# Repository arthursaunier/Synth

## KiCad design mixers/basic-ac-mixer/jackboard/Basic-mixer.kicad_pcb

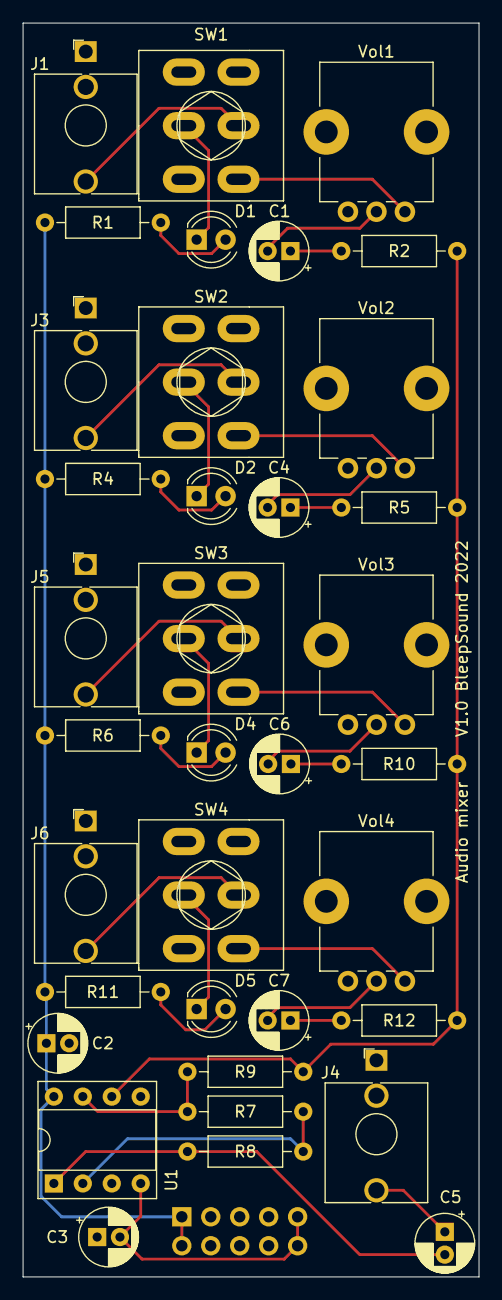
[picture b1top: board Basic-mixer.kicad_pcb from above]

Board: 2 copper layers, 40.0 x 110.0 mm, 37 parts (1 on the bottom side), 32 nets.

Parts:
C1, C4, C6, C7: .1µF; CP_Radial_D5.0mm_P2.00mm
C2, C3: 10µ; CP_Radial_D5.0mm_P2.00mm
C5: 10µF; CP_Radial_D5.0mm_P2.00mm
D1, D2, D4, D5: LED-mute; LED_D4.0mm
J1, J3, J5, J6: In; Thonkiconn
J2: Power Input; PinHeader_2x05_P2.54mm_Vertical
J4: Out; Thonkiconn
R1, R4, R6, R11: 4.7k; R_Axial_DIN0207_L6.3mm_D2.5mm_P10.16mm_Horizontal
R2, R5, R9, R10, R12: 100k; R_Axial_DIN0207_L6.3mm_D2.5mm_P10.16mm_Horizontal
R7, R8: 10k; R_Axial_DIN0207_L6.3mm_D2.5mm_P10.16mm_Horizontal
SW1, SW2, SW3, SW4: Mute; SW_DPDT_Toggle
U1: TL072; DIP-8_W7.62mm_Socket
Vol1, Vol2, Vol3, Vol4: 10k; Pot-bourns-alpha

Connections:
+12V: C2.1, J2.1, J2.2, R1.1, R4.1, R6.1, R11.1, U1.8 (V+)
-12V: C3.2, J2.9, J2.10, U1.4 (V-)
GND: C2.2, C3.1, J1.S, J2.3, J2.4, J2.5, J2.6, J2.7, J2.8, J3.S, J4.S, J5.S, J6.S, SW1.1 (A), SW2.1 (A), SW3.1 (A), SW4.1 (A), U1.3 (+), U1.5 (+), Vol1.3, Vol2.3, Vol3.3, Vol4.3
unnamed: C1.1, R2.2
unnamed: C1.2, Vol1.2
unnamed: C4.1, R5.2
unnamed: C4.2, Vol2.2
unnamed: C5.1, J4.T
unnamed: C5.2, R8.1, U1.1
unnamed: C6.1, R10.2
unnamed: C6.2, Vol3.2
unnamed: C7.1, R12.2
unnamed: C7.2, Vol4.2
unnamed: D1.1 (K), SW1.2 (B)
unnamed: D1.2 (A), R1.2
unnamed: D2.1 (K), SW2.2 (B)
unnamed: D2.2 (A), R4.2
unnamed: D4.1 (K), SW3.2 (B)
unnamed: D4.2 (A), R6.2
unnamed: D5.1 (K), SW4.2 (B)
unnamed: D5.2 (A), R11.2
unnamed: J1.T, SW1.5 (B)
unnamed: J3.T, SW2.5 (B)
unnamed: J5.T, SW3.5 (B)
unnamed: J6.T, SW4.5 (B)
unnamed: R7.1, R8.2, U1.2 (-)
unnamed: R7.2, R9.1, U1.7
unnamed: R2.1, R5.1, R9.2, R10.1, R12.1, U1.6 (-)
unnamed: SW1.6 (C), Vol1.1
unnamed: SW2.6 (C), Vol2.1
unnamed: SW3.6 (C), Vol3.1
unnamed: SW4.6 (C), Vol4.1

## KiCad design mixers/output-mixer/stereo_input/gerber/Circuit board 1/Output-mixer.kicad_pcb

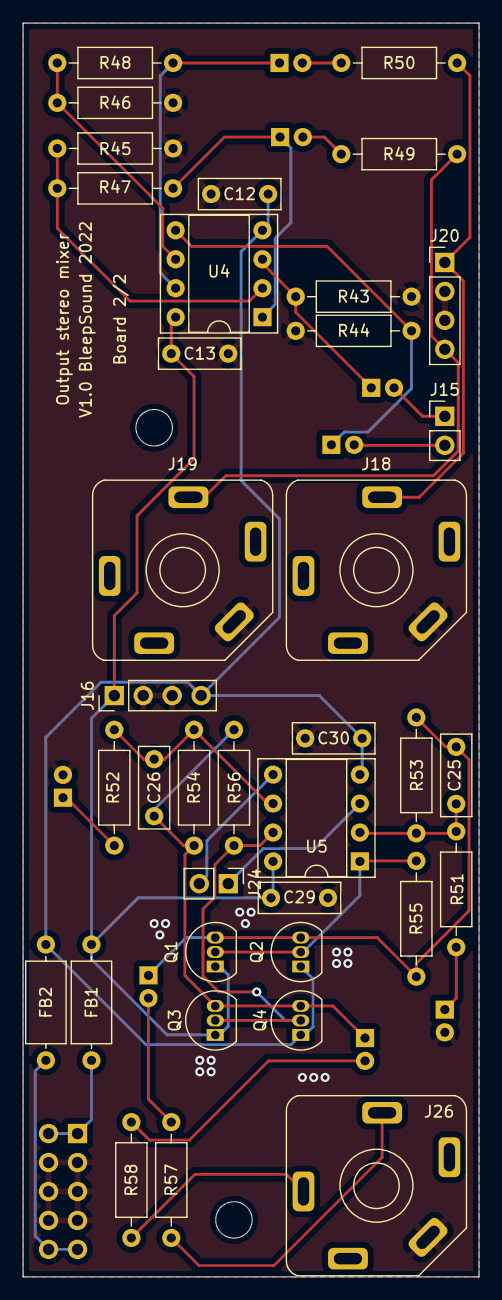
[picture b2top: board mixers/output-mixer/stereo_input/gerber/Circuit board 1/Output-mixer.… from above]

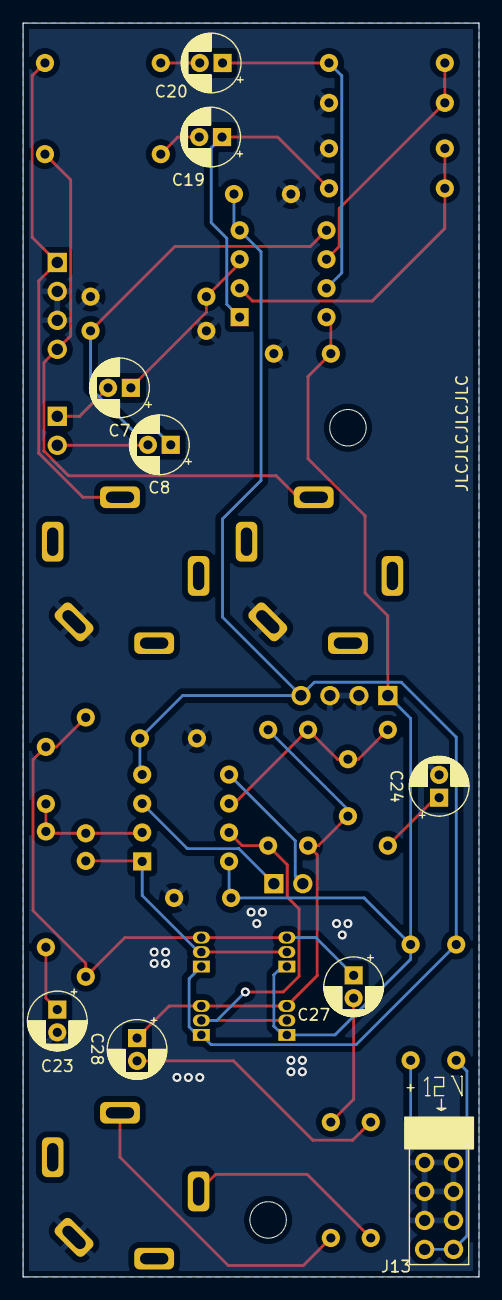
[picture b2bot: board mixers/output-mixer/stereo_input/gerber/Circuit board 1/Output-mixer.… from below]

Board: 2 copper layers, 40.0 x 110.0 mm, 48 parts (9 on the bottom side), 31 nets.

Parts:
C7, C8, C19, C20, C23, C24, C27, C28: 10µF; CP_Radial_D5.0mm_P2.00mm
C12, C13, C29, C30: 100nF; C_Disc_D7.0mm_W2.5mm_P5.00mm
C25, C26: 470pF; C_Disc_D7.0mm_W2.5mm_P5.00mm
FB1, FB2: 10R; L_Axial_L7.0mm_D3.3mm_P10.16mm_Horizontal_Fastron_MICC
H6, H8: SpacerHoles; MountingHole_3.2mm_M3
J13: Power Input; PinHeader_2x05_P2.54mm_Vertical
J15, J24: Conn_01x02_Male; PinHeader_1x02_P2.54mm_Vertical
J16: Conn_01x04_Male; PinHeader_1x04_P2.54mm_Vertical
J18: OutR; PJ-629HAN
J19: OutL; PJ-629HAN
J20: Jack 3.5 Out; PinHeader_1x04_P2.54mm_Vertical
J26: OutHeadStereo; PJ-629HAN
Q1, Q3: BC548; TO-92_Inline
Q2, Q4: BC558; TO-92_Inline
R43, R44, R45, R46, R47, R48: 100k; R_Axial_DIN0207_L6.3mm_D2.5mm_P10.16mm_Horizontal
R49, R50: 470R; R_Axial_DIN0207_L6.3mm_D2.5mm_P10.16mm_Horizontal
R51, R52: 1k; R_Axial_DIN0207_L6.3mm_D2.5mm_P10.16mm_Horizontal
R53, R54: 10k; R_Axial_DIN0207_L6.3mm_D2.5mm_P10.16mm_Horizontal
R55, R56: 560R; R_Axial_DIN0207_L6.3mm_D2.5mm_P10.16mm_Horizontal
R57, R58: 47R; R_Axial_DIN0207_L6.3mm_D2.5mm_P10.16mm_Horizontal
U4, U5: TL072; DIP-8_W7.62mm_Socket

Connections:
+12V: C13.1, C29.1, FB1.1, J16.1, Q1.1 (C), Q3.1 (C), U4.8 (V+), U5.8 (V+)
-12V: C12.2, C30.1, FB2.1, J16.4, Q2.1 (C), Q4.1 (C), U4.4 (V-), U5.4 (V-)
/AmpL: C7.2, J15.1
/AmpR: C8.2, J15.2
/Headphones Amp/Head-L: J26.T, R57.1
/Headphones Amp/Head-R: J26.R, R58.1
/Headphones Amp/HeadAmpL: J24.1, U5.3 (+)
/Headphones Amp/HeadAmpR: J24.2, U5.5 (+)
/OutL: J19.T, J20.4, R49.1
/OutR: J18.T, J20.1, R50.1
GND: C12.1, C13.2, C23.2, C24.2, C29.2, C30.2, J13.3, J13.4, J13.5, J13.6, J13.7, J13.8, J16.2, J16.3, J18.S, J19.S, J20.2, J20.3, J26.S, R43.1, R44.1, R45.1, R46.1
unnamed: C7.1, R43.2, U4.3 (+)
unnamed: C8.1, R44.2, U4.5 (+)
unnamed: C19.1, R47.1, U4.1
unnamed: C19.2, R49.2
unnamed: C20.1, R48.1, U4.7
unnamed: C20.2, R50.2
unnamed: C23.1, R51.1
unnamed: C24.1, R52.1
unnamed: C25.1, R51.2, R53.1, U5.2 (-)
unnamed: C25.2, C27.1, Q1.3 (E), Q2.3 (E), R53.2, R55.2
unnamed: C26.1, R52.2, R54.1, U5.6 (-)
unnamed: C26.2, C28.1, Q3.3 (E), Q4.3 (E), R54.2, R56.2
unnamed: C27.2, R57.2
unnamed: C28.2, R58.2
unnamed: FB1.2, J13.1, J13.2
unnamed: FB2.2, J13.9, J13.10
unnamed: Q1.2 (B), Q2.2 (B), R55.1, U5.1
unnamed: Q3.2 (B), Q4.2 (B), R56.1, U5.7
unnamed: R45.2, R47.2, U4.2 (-)
unnamed: R46.2, R48.2, U4.6 (-)

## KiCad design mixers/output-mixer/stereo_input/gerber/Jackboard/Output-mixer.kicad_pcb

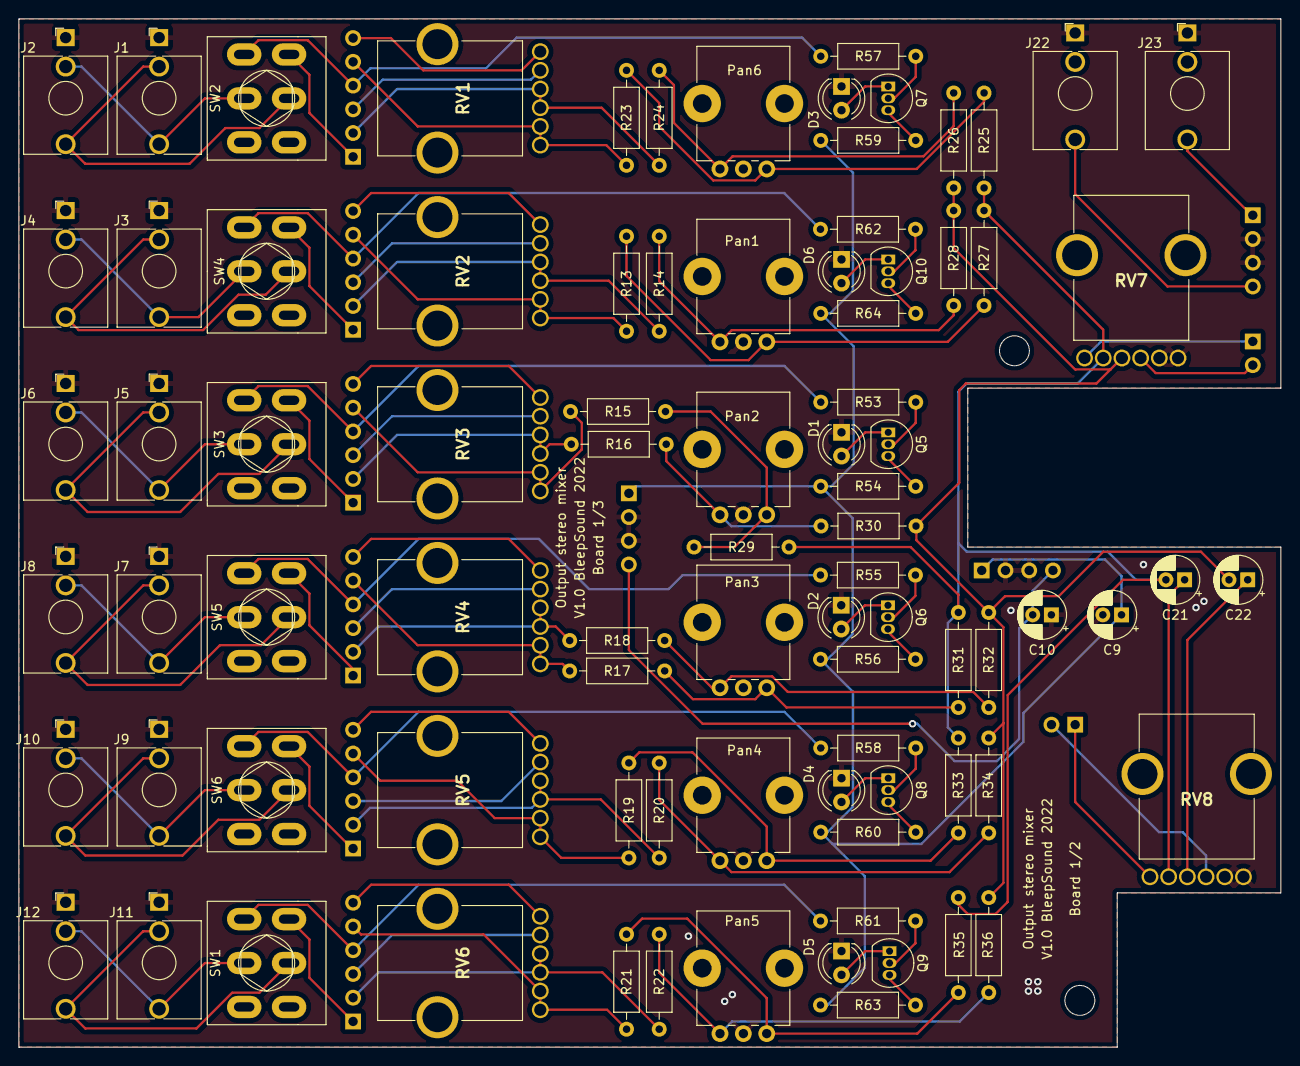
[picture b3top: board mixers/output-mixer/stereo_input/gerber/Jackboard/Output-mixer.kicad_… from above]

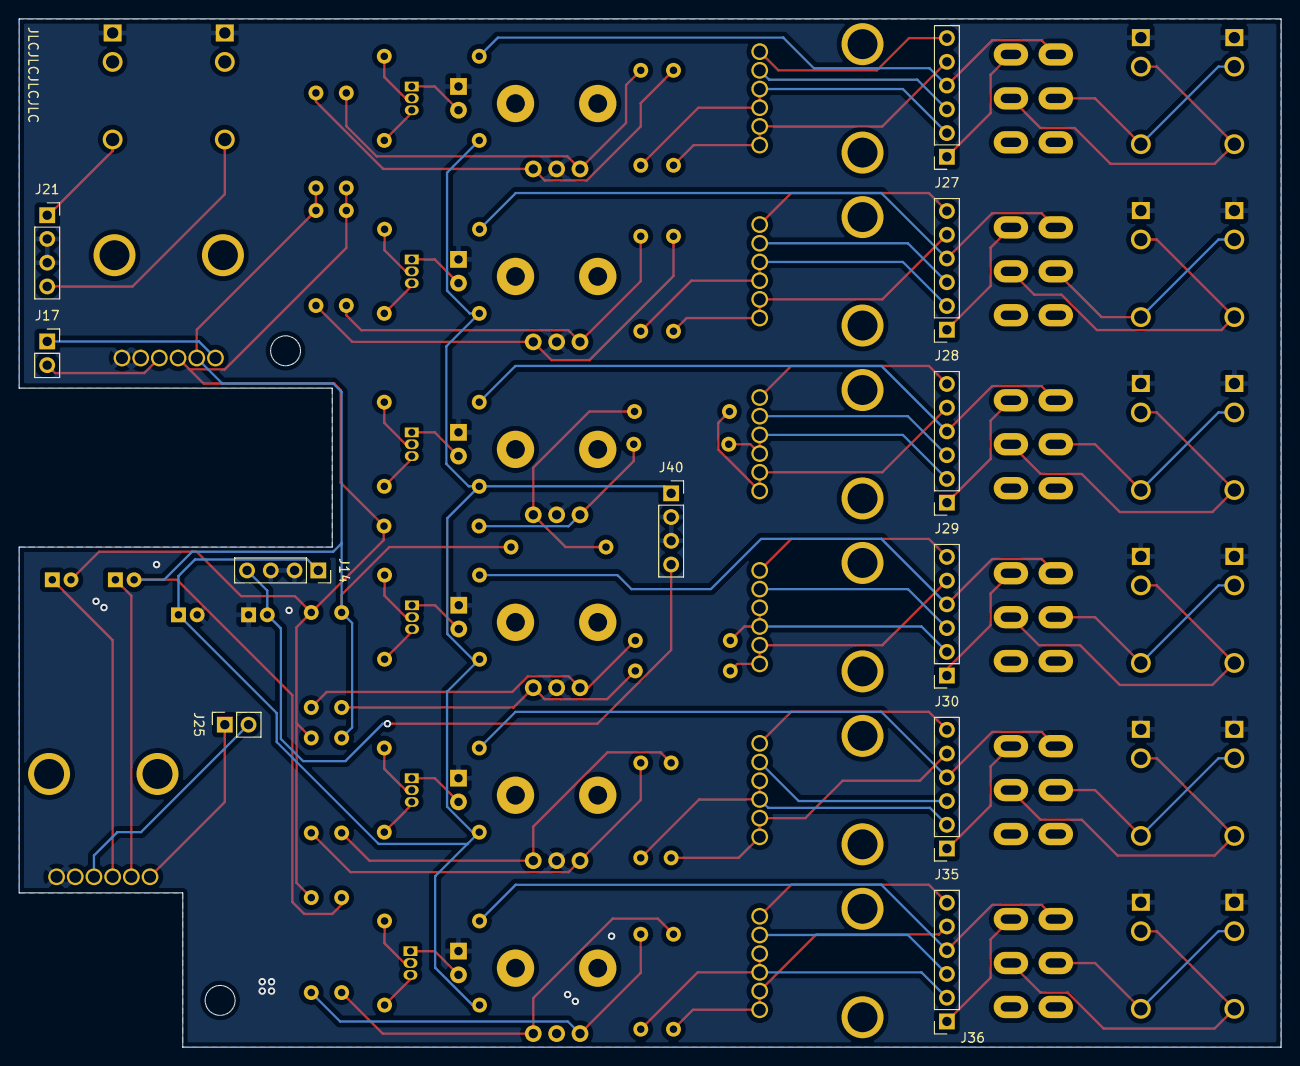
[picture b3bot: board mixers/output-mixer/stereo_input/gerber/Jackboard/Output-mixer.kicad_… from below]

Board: 2 copper layers, 135.0 x 110.0 mm, 99 parts (11 on the bottom side), 91 nets.

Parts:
C9, C10: 10µ; CP_Radial_D5.0mm_P2.00mm
C21, C22: 1µF; CP_Radial_D5.0mm_P2.00mm
D1, D2, D3, D4, D5, D6: Signal; LED_D4.0mm
H5, H7: SpacerHoles; MountingHole_3.2mm_M3
J1, J2, J3, J4, J5, J6, J7, J8, J9, J10, J11, J12: In; Thonkiconn
J14, J40: Conn_01x04_Female; PinSocket_1x04_P2.54mm_Vertical
J17, J25: Conn_01x02_Female; PinSocket_1x02_P2.54mm_Vertical
J21: Jack 3.5 Out; PinSocket_1x04_P2.54mm_Vertical
J22: OutL; Thonkiconn
J23: OutR; Thonkiconn
J27, J28, J29, J30, J35, J36: Conn_01x06_Female; PinSocket_1x06_P2.54mm_Vertical
Pan1, Pan2, Pan3, Pan4, Pan5, Pan6: 50k; Pot-bourns-alpha
Q5, Q6, Q7, Q8, Q9, Q10: 2N3904; TO-92_Inline
R13, R14, R15, R16, R17, R18, R19, R20, R21, R22, R23, R24: 2k2; R_Axial_DIN0207_L6.3mm_D2.5mm_P10.16mm_Horizontal
R25, R26, R27, R28, R29, R30, R31, R32, R33, R34, R35, R36: 47k; R_Axial_DIN0207_L6.3mm_D2.5mm_P10.16mm_Horizontal
R53, R55, R57, R58, R61, R62: 100k; R_Axial_DIN0207_L6.3mm_D2.5mm_P10.16mm_Horizontal
R54, R56, R59, R60, R63, R64: 1k; R_Axial_DIN0207_L6.3mm_D2.5mm_P10.16mm_Horizontal
RV1, RV2, RV3, RV4, RV5, RV6, RV7, RV8: 50k; PTV1124420AA503
SW1, SW2, SW3, SW4, SW5, SW6: Mute; SW_DPDT_Toggle

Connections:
+12V: C9.1, J14.1, J40.1, R54.1, R56.1, R59.1, R60.1, R63.1, R64.1
-12V: C10.2, J14.4, J40.4
/AmpL: J17.1, RV7.2
/AmpR: J17.2, RV7.5
/Headphones Amp/HeadAmpL: J25.1, RV8.2
/Headphones Amp/HeadAmpR: J25.2, RV8.5
/OutL: J21.4, J22.T
/OutR: J21.1, J23.T
GND: C9.2, C10.1, D1.1 (K), D2.1 (K), D3.1 (K), D4.1 (K), D5.1 (K), D6.1 (K), J1.S, J2.S, J3.S, J4.S, J5.S, J6.S, J7.S, J8.S, J9.S, J10.S, J11.S, J12.S, J14.2, J14.3, J21.2, J21.3, J22.S, J23.S, J40.2, J40.3, Pan1.2, Pan2.2, Pan3.2, Pan4.2, Pan5.2, Pan6.2, RV7.3, RV7.6, RV8.3, RV8.6
L: C21.2, R25.2, R27.2, R29.2, R31.2, R33.2, R35.2, RV7.1
Left1_GOut: J27.3, RV1.6
Left1_In: J27.1, SW2.4 (A)
Left1_Out: J27.2, R24.2, RV1.4, RV1.5
Left2_GOut: J28.3, RV2.6
Left2_In: J28.1, SW4.4 (A)
Left2_Out: J28.2, R14.2, RV2.4, RV2.5
Left3_GOut: J29.3, RV3.6
Left3_In: J29.1, SW3.4 (A)
Left3_Out: J29.2, R16.2, RV3.4, RV3.5
Left4_GOut: J30.3, RV4.6
Left4_In: J30.1, SW5.4 (A)
Left4_Out: J30.2, R18.2, RV4.4, RV4.5
Left5_GOut: J35.3, RV5.6
Left5_In: J35.1, SW6.4 (A)
Left5_Out: J35.2, R20.2, RV5.4, RV5.5
Left6_GOut: J36.3, RV6.6
Left6_In: J36.1, SW1.4 (A)
Left6_Out: J36.2, R22.2, RV6.4, RV6.5
unnamed: C21.1, RV8.1
unnamed: C22.1, RV8.4
unnamed: D1.2 (A), Q5.1 (E)
unnamed: D2.2 (A), Q6.1 (E)
unnamed: D3.2 (A), Q7.1 (E)
unnamed: D4.2 (A), Q8.1 (E)
unnamed: D5.2 (A), Q9.1 (E)
unnamed: D6.2 (A), Q10.1 (E)
unnamed: J1.T, J2.TN, SW2.2 (B)
unnamed: J1.TN, J2.T, SW2.5 (B)
unnamed: J3.T, J4.TN, SW4.2 (B)
unnamed: J3.TN, J4.T, SW4.5 (B)
unnamed: J5.T, J6.TN, SW3.2 (B)
unnamed: J5.TN, J6.T, SW3.5 (B)
unnamed: J7.T, J8.TN, SW5.2 (B)
unnamed: J7.TN, J8.T, SW5.5 (B)
unnamed: J9.TN, J10.T, SW6.5 (B)
unnamed: J9.T, J10.TN, SW6.2 (B)
unnamed: J11.T, J12.TN, SW1.2 (B)
unnamed: J11.TN, J12.T, SW1.5 (B)
unnamed: Pan1.1, R13.2, R27.1
unnamed: Pan1.3, R14.1, R28.2
unnamed: Pan2.1, R15.2, R29.1
unnamed: Pan2.3, R16.1, R30.2
unnamed: Pan3.1, R17.2, R31.1
unnamed: Pan3.3, R18.1, R32.2
unnamed: Pan4.1, R19.2, R33.1
unnamed: Pan4.3, R20.1, R34.2
unnamed: Pan5.1, R21.2, R35.1
unnamed: Pan5.3, R22.1, R36.2
unnamed: Pan6.1, R23.2, R25.1
unnamed: Pan6.3, R24.1, R26.2
unnamed: Q5.2 (B), R53.2
unnamed: Q5.3 (C), R54.2
unnamed: Q6.2 (B), R55.2
unnamed: Q6.3 (C), R56.2
unnamed: Q7.2 (B), R57.2
unnamed: Q7.3 (C), R59.2
unnamed: Q8.2 (B), R58.2
unnamed: Q8.3 (C), R60.2
unnamed: Q9.2 (B), R61.2
unnamed: Q9.3 (C), R63.2
unnamed: Q10.2 (B), R62.2
unnamed: Q10.3 (C), R64.2
R: C22.2, R26.1, R28.1, R30.1, R32.1, R34.1, R36.1, RV7.4
Right1_GOut: J27.6, RV1.3
Right1_In: J27.4, R57.1, SW2.1 (A)
Right1_Out: J27.5, R23.1, RV1.1, RV1.2
Right2_GOut: J28.6, RV2.3
Right2_In: J28.4, R62.1, SW4.1 (A)
Right2_Out: J28.5, R13.1, RV2.1, RV2.2
Right3_GOut: J29.6, RV3.3
Right3_In: J29.4, R53.1, SW3.1 (A)
Right3_Out: J29.5, R15.1, RV3.1, RV3.2
Right4_GOut: J30.6, RV4.3
Right4_In: J30.4, R55.1, SW5.1 (A)
Right4_Out: J30.5, R17.1, RV4.1, RV4.2
Right5_GOut: J35.6, RV5.3
Right5_In: J35.4, R58.1, SW6.1 (A)
Right5_Out: J35.5, R19.1, RV5.1, RV5.2
Right6_GOut: J36.6, RV6.3
Right6_In: J36.4, R61.1, SW1.1 (A)
Right6_Out: J36.5, R21.1, RV6.1, RV6.2

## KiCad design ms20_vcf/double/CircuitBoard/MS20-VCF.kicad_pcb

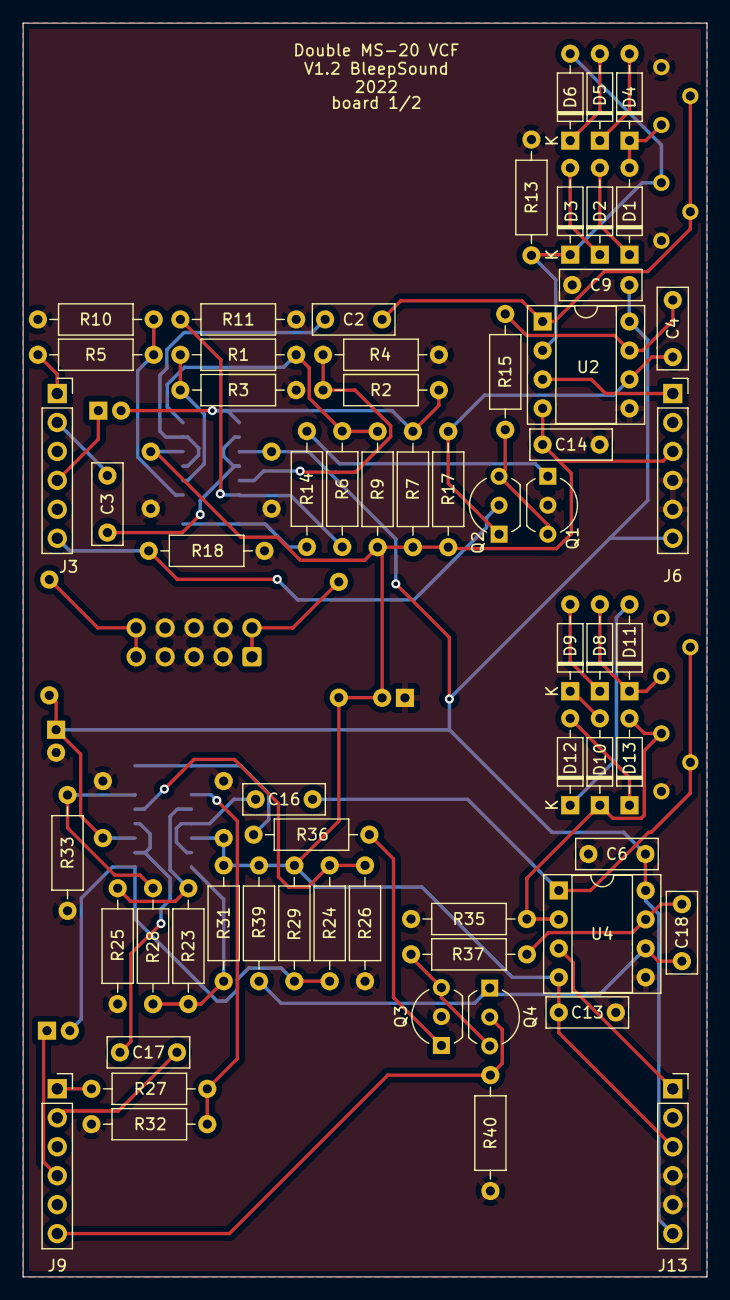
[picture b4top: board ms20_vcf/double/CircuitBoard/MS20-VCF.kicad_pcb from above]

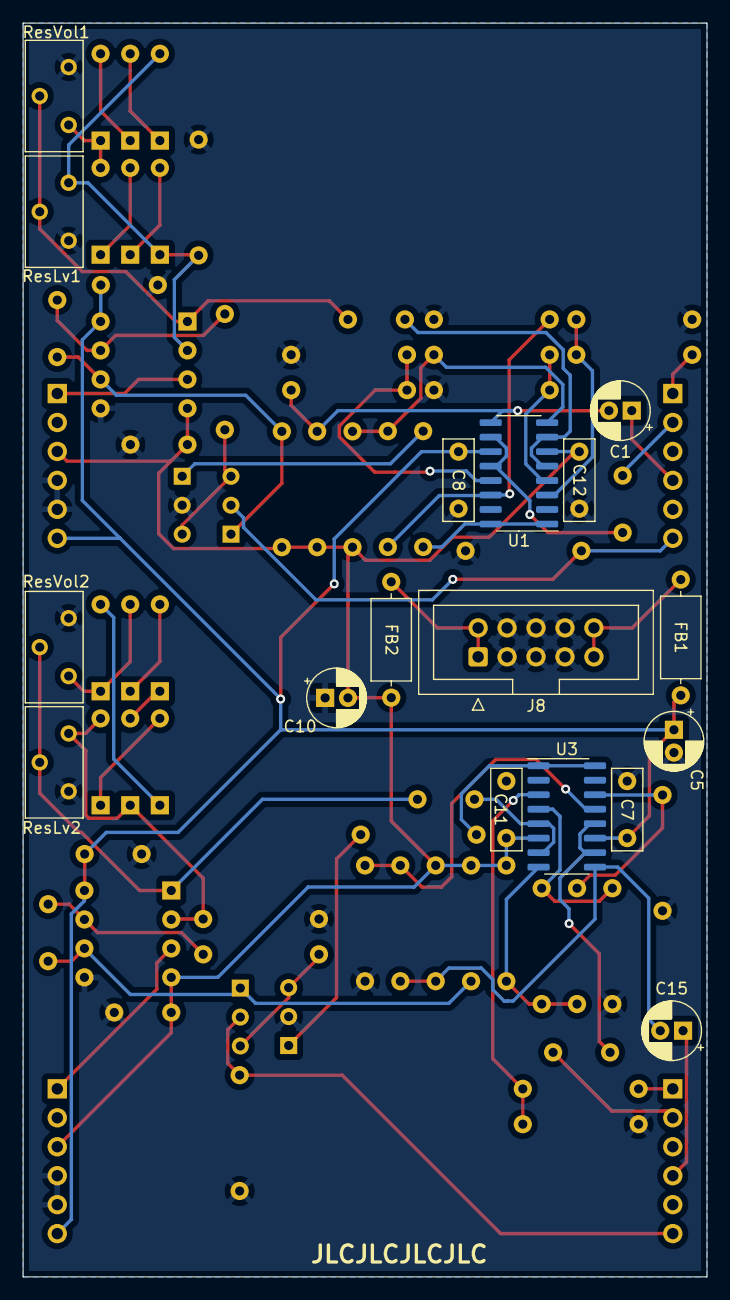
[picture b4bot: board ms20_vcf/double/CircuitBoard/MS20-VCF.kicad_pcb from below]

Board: 2 copper layers, 60.0 x 110.0 mm, 79 parts (17 on the bottom side), 55 nets.

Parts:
C1, C15: 10µF; CP_Radial_D5.0mm_P2.00mm
C2, C3, C4, C16, C17, C18: 1nF; C_Disc_D7.0mm_W2.5mm_P5.00mm
C5, C10: 10µ; CP_Radial_D5.0mm_P2.00mm
C6, C7, C8, C9, C11, C12, C13, C14: 100nF; C_Disc_D7.0mm_W2.5mm_P5.00mm
D1, D2, D3, D4, D5, D6, D8, D9, D10, D11, D12, D13: 1N4148; D_DO-35_SOD27_P7.62mm_Horizontal
FB1, FB2: 10R; L_Axial_L7.0mm_D3.3mm_P10.16mm_Horizontal_Fastron_MICC
J3, J6, J9, J13: Conn_CircuitBoard; PinSocket_1x06_P2.54mm_Vertical
J8: Power Input; IDC-Header_2x05_P2.54mm_Vertical
Q1, Q2, Q3, Q4: BC559; TO-92_Inline_Wide
R1, R2, R5, R6, R17, R23, R24, R27, R28, R39: 100k; R_Axial_DIN0207_L6.3mm_D2.5mm_P10.16mm_Horizontal
R3, R4, R10, R11, R25, R26, R32, R33: 470; R_Axial_DIN0207_L6.3mm_D2.5mm_P10.16mm_Horizontal
R7, R9, R29, R31: 1.8k; R_Axial_DIN0207_L6.3mm_D2.5mm_P10.16mm_Horizontal
R13, R14, R18, R35, R36, R40: 2.2k; R_Axial_DIN0207_L6.3mm_D2.5mm_P10.16mm_Horizontal
R15, R37: 1k; R_Axial_DIN0207_L6.3mm_D2.5mm_P10.16mm_Horizontal
ResLv1: 5k; Potentiometer_Bourns_3386X_Horizontal
ResLv2: 3.3k; Potentiometer_Bourns_3386X_Horizontal
ResVol1, ResVol2: 10k; Potentiometer_Bourns_3386X_Horizontal
U1, U3: LM13700; SOIC-16_3.9x9.9mm_P1.27mm
U2, U4: TL072; DIP-8_W7.62mm_Socket

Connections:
+12V: C5.1, C6.1, C7.1, C8.1, C9.1, FB1.1, J6.6, J13.6, U1.11 (V+), U2.8 (V+), U3.11 (V+), U4.8 (V+)
-12V: C10.2, C11.2, C12.2, C13.2, C14.2, FB2.1, J6.3, J13.3, R7.1, R9.1, R17.1, R29.1, R31.1, R39.1, U1.6 (V-), U2.4 (V-), U3.6 (V-), U4.4 (V-)
/Cutoff: J3.6, Q2.2 (B), R18.2
/Filtre2/Cutoff: J9.6, Q4.2 (B), R40.2
/Filtre2/HPass: C17.2, J9.2
/Filtre2/LPass: J9.1, R27.1
/Filtre2/Out1: C15.1, J9.4
/Filtre2/ResOut: J13.1, U4.3 (+)
/HPass: C3.2, J3.2
/LPass: J3.1, R5.1
/Out1: C1.1, J3.4
/ResOut: J6.1, U2.3 (+)
GND: C5.2, C6.2, C7.2, C8.2, C9.2, C10.1, C11.1, C12.1, C13.1, C14.1, J6.4, J6.5, J8.3, J8.4, J8.5, J8.6, J8.7, J8.8, J13.4, J13.5, Q1.2 (B), Q3.2 (B), R3.1, R4.1, R10.1, R11.1, R13.1, R18.1, R25.1, R26.1, R32.1, R33.1, R35.1, R40.1, ResLv1.1, ResLv2.1, ResVol1.3, ResVol2.3, U2.5 (+), U4.5 (+)
unnamed: C1.2, R2.2, R7.2, U1.9
unnamed: C2.1, U1.5, U1.7
unnamed: C2.2, ResLv1.2, ResVol1.2, U2.1
unnamed: C3.1, U1.10, U1.12
unnamed: C4.1, R15.2, U2.7
unnamed: C4.2, Q2.1 (C), R17.2, U2.6 (-)
unnamed: C15.2, R24.2, R29.2, U3.9
unnamed: C16.1, U3.5, U3.7
unnamed: C16.2, ResLv2.2, ResVol2.2, U4.1
unnamed: C17.1, U3.10, U3.12
unnamed: C18.1, R37.2, U4.7
unnamed: C18.2, Q4.1 (C), R39.2, U4.6 (-)
unnamed: D1.1 (K), D2.2 (A)
unnamed: D1.2 (A), D4.1 (K), ResVol1.1
unnamed: D2.1 (K), D3.2 (A)
unnamed: D3.1 (K), D6.2 (A), R13.2, ResLv1.3, U2.2 (-)
unnamed: D4.2 (A), D5.1 (K)
unnamed: D5.2 (A), D6.1 (K)
unnamed: D8.1 (K), D9.2 (A)
unnamed: D10.1 (K), D13.2 (A), R35.2, ResLv2.3, U4.2 (-)
unnamed: D9.1 (K), D10.2 (A)
unnamed: D8.2 (A), D11.1 (K), ResVol2.1
unnamed: D11.2 (A), D12.1 (K)
unnamed: D12.2 (A), D13.1 (K)
unnamed: FB1.2, J8.9, J8.10
unnamed: FB2.2, J8.1, J8.2
unnamed: Q1.1 (C), R14.1
unnamed: Q1.3 (E), Q2.3 (E), R15.1
unnamed: Q3.1 (C), R36.1
unnamed: Q3.3 (E), Q4.3 (E), R37.1
unnamed: R1.1, R3.2, U1.4 (-)
unnamed: R1.2, R6.1, R9.2, U1.8
unnamed: R2.1, R4.2, U1.13 (-)
unnamed: R5.2, R10.2, U1.3 (+)
unnamed: R6.2, R11.2, U1.14 (+)
unnamed: R14.2, U1.1, U1.16
unnamed: R23.1, R25.2, U3.4 (-)
unnamed: R23.2, R28.1, R31.2, U3.8
unnamed: R24.1, R26.2, U3.13 (-)
unnamed: R27.2, R32.2, U3.3 (+)
unnamed: R28.2, R33.2, U3.14 (+)
unnamed: R36.2, U3.1, U3.16

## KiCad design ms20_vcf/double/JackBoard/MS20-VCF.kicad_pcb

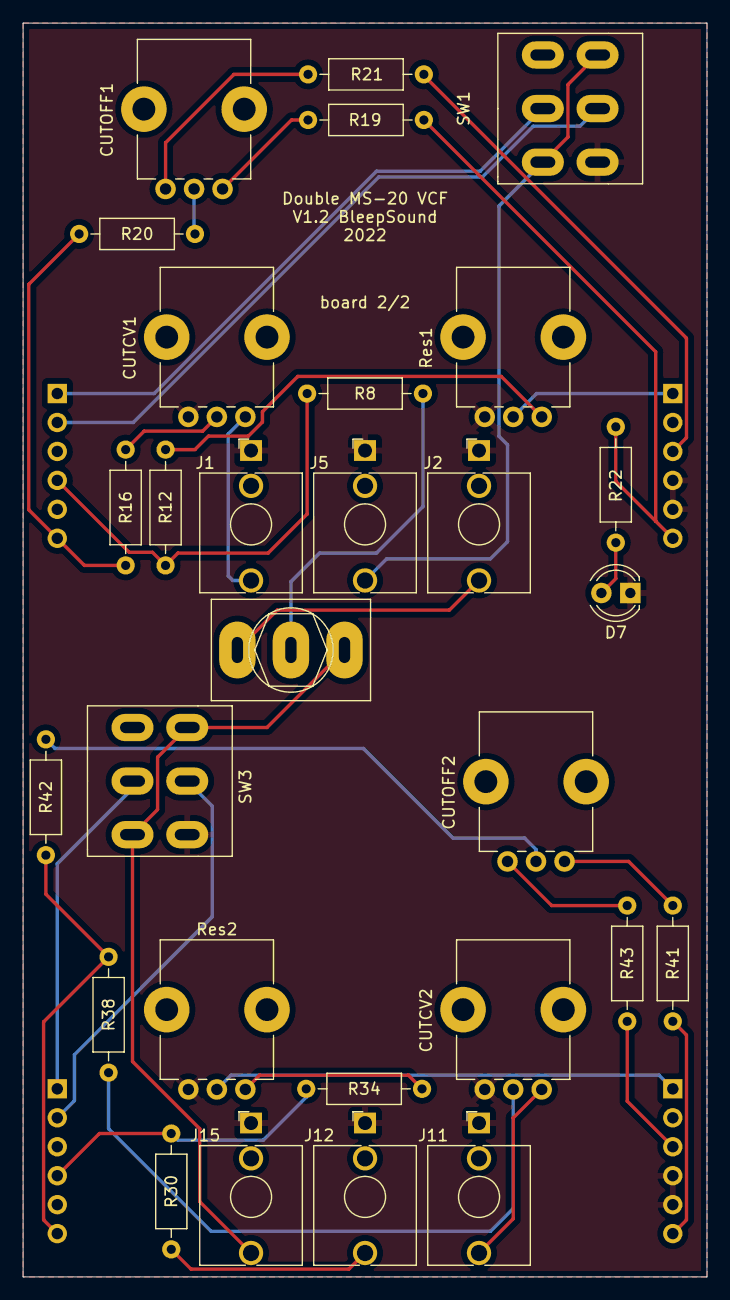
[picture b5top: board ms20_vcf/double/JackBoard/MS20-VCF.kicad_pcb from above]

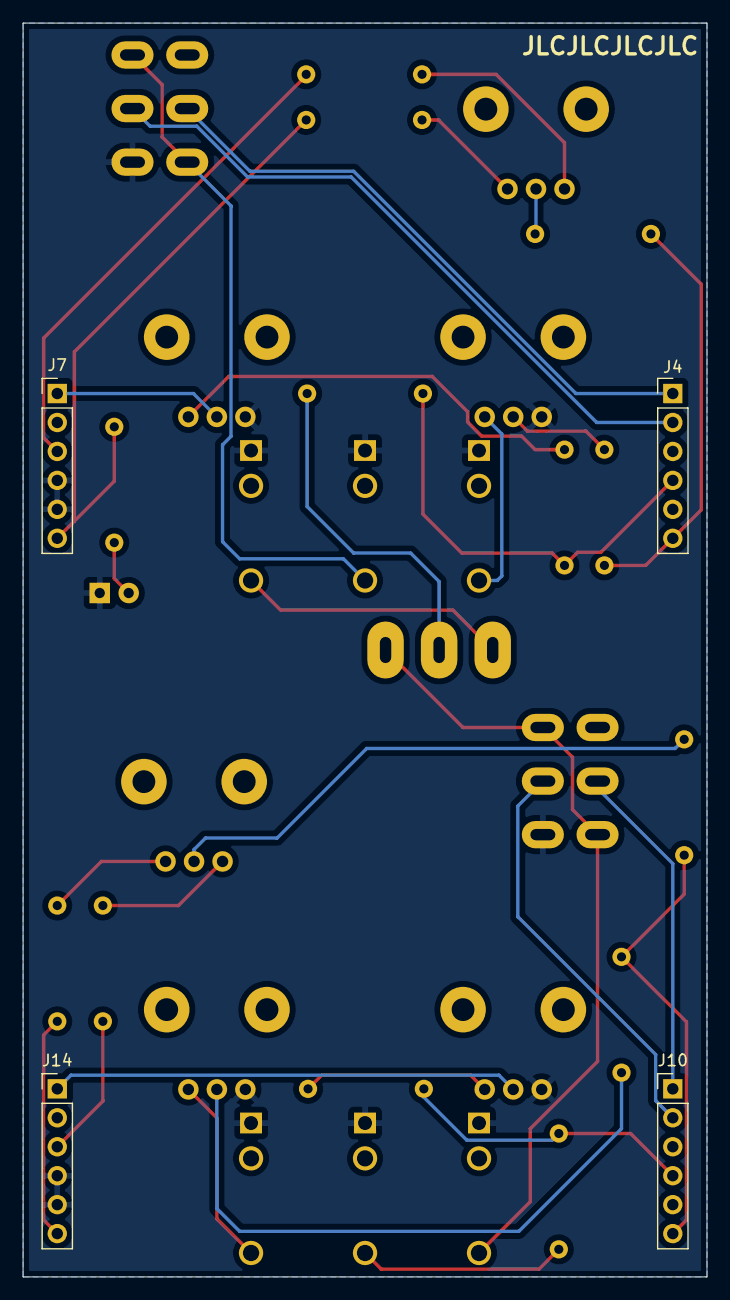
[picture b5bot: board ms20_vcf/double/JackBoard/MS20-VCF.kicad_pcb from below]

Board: 2 copper layers, 60.0 x 110.0 mm, 33 parts (4 on the bottom side), 31 nets.

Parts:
CUTCV1, CUTCV2: 100k; Pot-bourns-alpha
CUTOFF1, CUTOFF2: 100k; Pot-bourns-alpha
D7: LED-12V; LED_D4.0mm
J1: FilterCV1; Thonkiconn
J2: FilterOut1; Thonkiconn
J4, J7, J10, J14: Conn_JackBoard; PinHeader_1x06_P2.54mm_Vertical
J5: FilterIn1; Thonkiconn
J11: FilterCV2; Thonkiconn
J12: FilterOut2; Thonkiconn
J15: FilterIn2; Thonkiconn
R8, R12, R30, R34: 1k; R_Axial_DIN0207_L6.3mm_D2.5mm_P10.16mm_Horizontal
R16, R38: 82k; R_Axial_DIN0207_L6.3mm_D2.5mm_P10.16mm_Horizontal
R19, R41: 33k; R_Axial_DIN0207_L6.3mm_D2.5mm_P10.16mm_Horizontal
R20, R42: 100k; R_Axial_DIN0207_L6.3mm_D2.5mm_P10.16mm_Horizontal
R21, R43: 56k; R_Axial_DIN0207_L6.3mm_D2.5mm_P10.16mm_Horizontal
R22: 2.2k; R_Axial_DIN0207_L6.3mm_D2.5mm_P10.16mm_Horizontal
Res1, Res2: 100k; Pot-bourns-alpha
SW1, SW3: Hpass/Lpass Switch; SW_DPDT_Toggle
SW2: Bandpass; SW_Toggle_Blue_wSlots

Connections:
+12V: J7.6, J14.6, R19.2, R22.1, R41.2
-12V: J7.3, J14.3, R21.1, R43.1
/CVIn: CUTCV1.1, J1.T
/Cutoff: J4.6, R16.1, R20.1
/FilterIn: J5.T, SW1.3 (C), SW1.4 (A)
/FilterOut: R8.1, SW2.2 (B)
/Filtre2/CVIn: CUTCV2.1, J11.T
/Filtre2/Cutoff: J10.6, R38.1, R42.1
/Filtre2/FilterOut: J12.T, R30.1
/Filtre2/HPass: J10.2, SW3.5 (B)
/Filtre2/LPass: J10.1, SW3.2 (B)
/Filtre2/Out1: J10.4, R30.2, R34.2
/Filtre2/ResOut: J14.1, Res2.2
/HPass: J4.2, SW1.5 (B)
/JackOut: J2.T, SW2.1 (A)
/LPass: J4.1, SW1.2 (B)
/Out1: J4.4, R8.2, R12.2
/ResOut: J7.1, Res1.2
Filter2In: J15.T, SW2.3 (C), SW3.3 (C), SW3.4 (A)
GND: CUTCV1.3, CUTCV2.3, D7.1 (K), J1.S, J2.S, J5.S, J7.4, J7.5, J11.S, J12.S, J14.4, J14.5, J15.S, Res1.3, Res2.3, SW1.6 (C), SW3.6 (C)
unnamed: CUTCV1.2, R16.2
unnamed: CUTCV2.2, R38.2
unnamed: CUTOFF1.1, R19.1
unnamed: CUTOFF2.1, R41.1
unnamed: CUTOFF2.2, R42.2
unnamed: CUTOFF2.3, R43.2
unnamed: D7.2 (A), R22.2
unnamed: R12.1, Res1.1
unnamed: CUTOFF1.2, R20.2
unnamed: CUTOFF1.3, R21.2
unnamed: R34.1, Res2.1
